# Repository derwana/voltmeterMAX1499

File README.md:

# voltmeterMAX1499
The voltmeterMAX1499 is - as you may expect by the name - a voltmeter based on the MAX1499 chip by maximinterated.

Started as a university project (v1) to be put into the student laboratories consoles as a highly accurat voltmeter (guess what: it never happend), it later got reworked (v2) to be used with a refrence voltage and two different seven-segment-display-boards.

## 1 precepts
1. boards for the IC and the 'display' have to be seperate
2. board dimensions not given, but as small as possible
3. six seven-segments – one for the '-' and five for the digits
4. multiple options for displaying (0kR for selection)
	1. decimals by chip
	2. decimals by user
5. boards to be connected by male and female headers
6. drills for spacers and mounting
7. use smd parts

## 2 prototype pictures

## 3 prototype testing
on X3: 5V DC (Vcc)
on X1: 1.000V DC (testvoltage by signalgenerator)

Measuring the current consumption is a good tool to determin a correctly working board.

One seven-segment-element consumes 20mA on max brightness and all tiles lit. Six of them are used, so a current consumption of ca. 120mA is expected.

With R3=24kR and displaying 18882, the current flowing is 117mA.
On idle, current consumption as expected of the datasheet.

## 4 Costs
estimated 45,00 € (per unit)
* PCBs 16.65€
* MAX1499 13.10€
* 7-Segments 1.00€-2.00€ (per segment-unit)

## 5 pictures of v2
Connections:
* potentiometer for dimming (black/pink)
* Vcc (black/red)
* voltage to measure (black/orange)
* programming interface (brown/red/orange/yellow)

## 6 further possible improvements (by programming)
* moving decimal point
* using internal reference of MAX1499
* reading measurements over serial

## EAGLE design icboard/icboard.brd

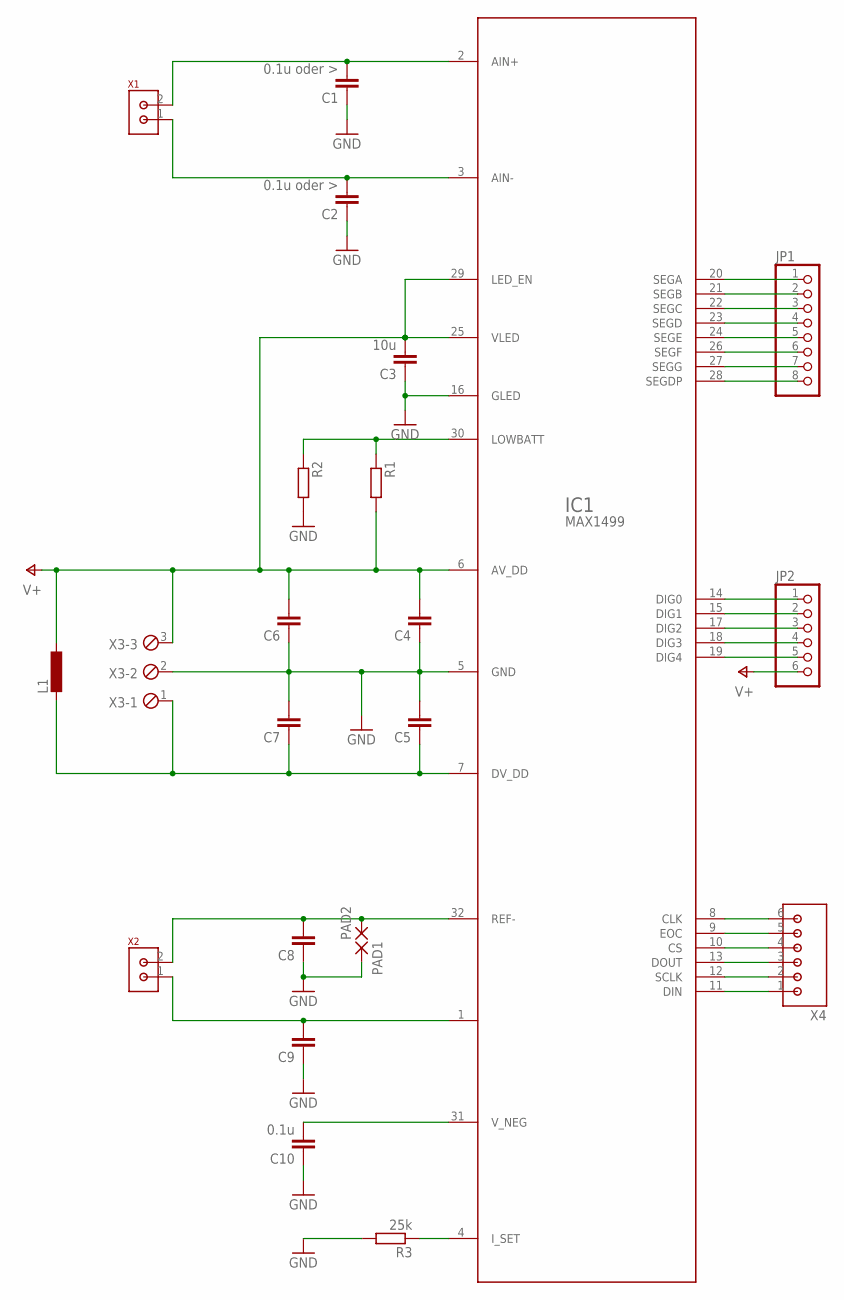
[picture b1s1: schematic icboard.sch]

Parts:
C1, C2: 0.1u oder >; C0603
C3: 10u; C0603
C4, C5, C6, C7, C8, C9: C-EUC0603; C0603
C10: 0.1u; C0603
IC1: MAX1499; TQFP32-08
JP1: PINHD-1X8; 1X08
JP2: PINHD-1X6; 1X06
L1: L-EUL1812; L1812
PAD1, PAD2: SMD2; SMD1,27-2,54
R1, R2: R-EU_R0603; R0603
R3: 25k; R0603
X1, X2: MOLEX_CON2_2P; CON2_2P
X3: MPT3; 3POL254
X4: MOLEX_CON2_6P; CON2_6P

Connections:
GND: C1.1, C2.1, C3.1, C4.1, C5.2, C6.1, C7.2, C8.1, C9.1, C10.1, IC1.5 (GND), IC1.16 (GLED), PAD1.1, R2.2, R3.2, X3.2
unnamed: C1.2, IC1.2 (AIN+), X1.2
unnamed: C2.2, IC1.3 (AIN-), X1.1
unnamed: IC1.17 (DIG2), JP2.3
unnamed: IC1.30 (LOWBATT), R1.1, R2.1
unnamed: C5.1, C7.1, IC1.7 (DV_DD), L1.2, X3.1
unnamed: C8.2, IC1.32 (REF-), PAD2.1, X2.2
unnamed: C9.2, IC1.1 (REF+), X2.1
unnamed: IC1.4 (I_SET), R3.1
unnamed: C10.2, IC1.31 (V_NEG)
unnamed: IC1.20 (SEGA), JP1.1
unnamed: IC1.21 (SEGB), JP1.2
unnamed: IC1.22 (SEGC), JP1.3
unnamed: IC1.23 (SEGD), JP1.4
unnamed: IC1.24 (SEGE), JP1.5
unnamed: IC1.26 (SEGF), JP1.6
unnamed: IC1.27 (SEGG), JP1.7
unnamed: IC1.28 (SEGDP), JP1.8
unnamed: IC1.14 (DIG0), JP2.1
unnamed: IC1.15 (DIG1), JP2.2
unnamed: IC1.18 (DIG3), JP2.4
unnamed: IC1.19 (DIG4), JP2.5
unnamed: IC1.9 (EOC), X4.5
unnamed: IC1.13 (DOUT), X4.3
unnamed: IC1.12 (SCLK), X4.2
unnamed: IC1.10 (CS), X4.4
unnamed: IC1.11 (DIN), X4.1
unnamed: IC1.8 (CLK), X4.6
V+: C3.2, C4.2, C6.2, IC1.6 (AV_DD), IC1.25 (VLED), IC1.29 (LED_EN), JP2.6, L1.1, R1.2, X3.3

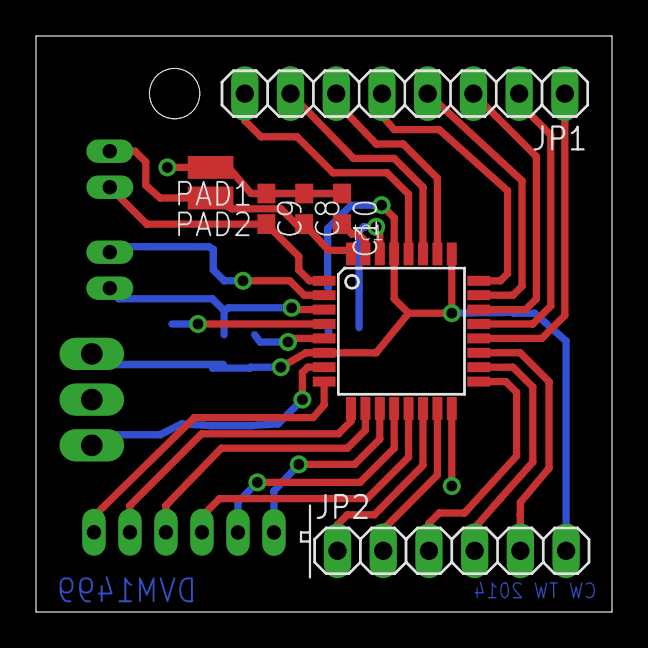
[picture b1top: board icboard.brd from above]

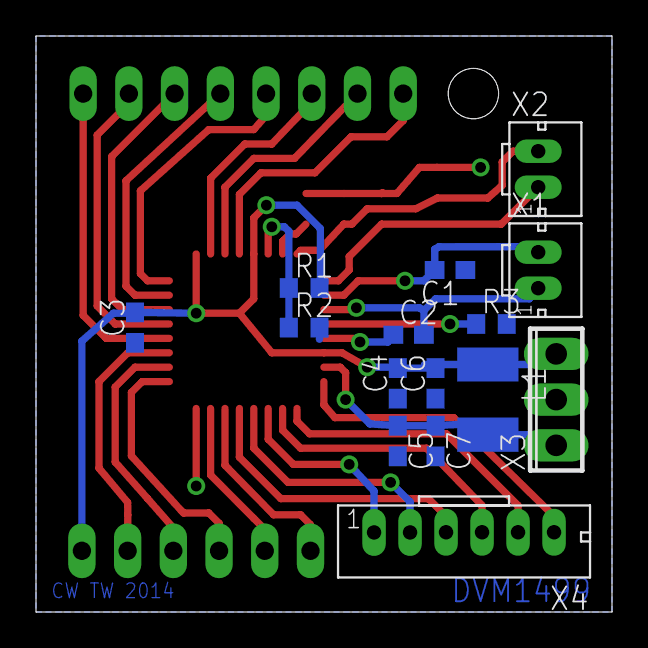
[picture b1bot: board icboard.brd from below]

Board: 2 copper layers, 32.0 x 32.0 mm, 23 parts (15 on the bottom side), 29 nets.

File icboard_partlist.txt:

Partlist

Assembly variant: 

Part     Value          Device        Package      Library         Sheet

C1       0.1u oder >    C-EUC0603     C0603        rcl             1
C2       0.1u oder >    C-EUC0603     C0603        rcl             1
C3       10u            C-EUC0603     C0603        rcl             1
C4                      C-EUC0603     C0603        rcl             1
C5                      C-EUC0603     C0603        rcl             1
C6                      C-EUC0603     C0603        rcl             1
C7                      C-EUC0603     C0603        rcl             1
C8                      C-EUC0603     C0603        rcl             1
C9                      C-EUC0603     C0603        rcl             1
C10      0.1u           C-EUC0603     C0603        rcl             1
IC1      MAX1499        MAX1499       TQFP32-08    LEDVoltmeter    1
JP1                     PINHD-1X8     1X08         pinhead         1
JP2                     PINHD-1X6     1X06         pinhead         1
L1                      L-EUL1812     L1812        rcl             1
PAD1                    SMD2          SMD1,27-2,54 wirepad         1
PAD2                    SMD2          SMD1,27-2,54 wirepad         1
R1                      R-EU_R0603    R0603        rcl             1
R2                      R-EU_R0603    R0603        rcl             1
R3       25k            R-EU_R0603    R0603        rcl             1
X1       MOLEX_CON2_2P  MOLEX_CON2_2P CON2_2P      Lib_Eis_HSW     1
X2       MOLEX_CON2_2P  MOLEX_CON2_2P CON2_2P      Lib_Eis_HSW     1
X3                      MPT3          3POL254      con-phoenix-254 1
X4                      MOLEX_CON2_6P CON2_6P      Lib_Eis_HSW     1

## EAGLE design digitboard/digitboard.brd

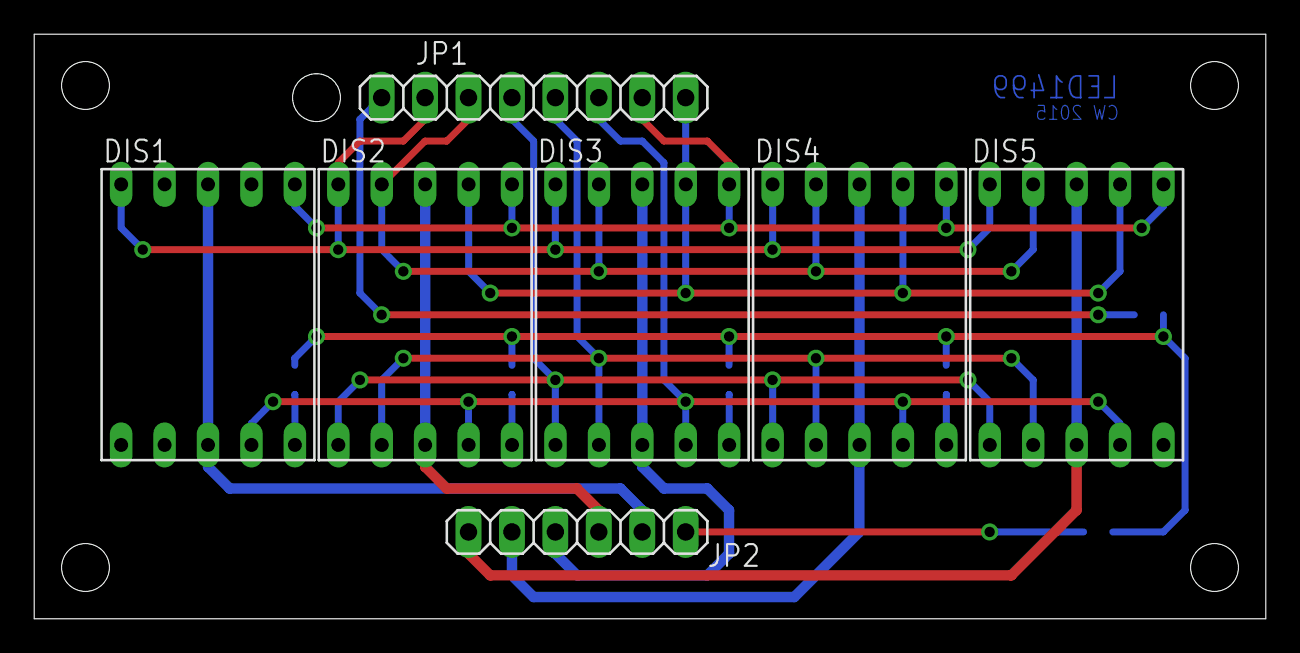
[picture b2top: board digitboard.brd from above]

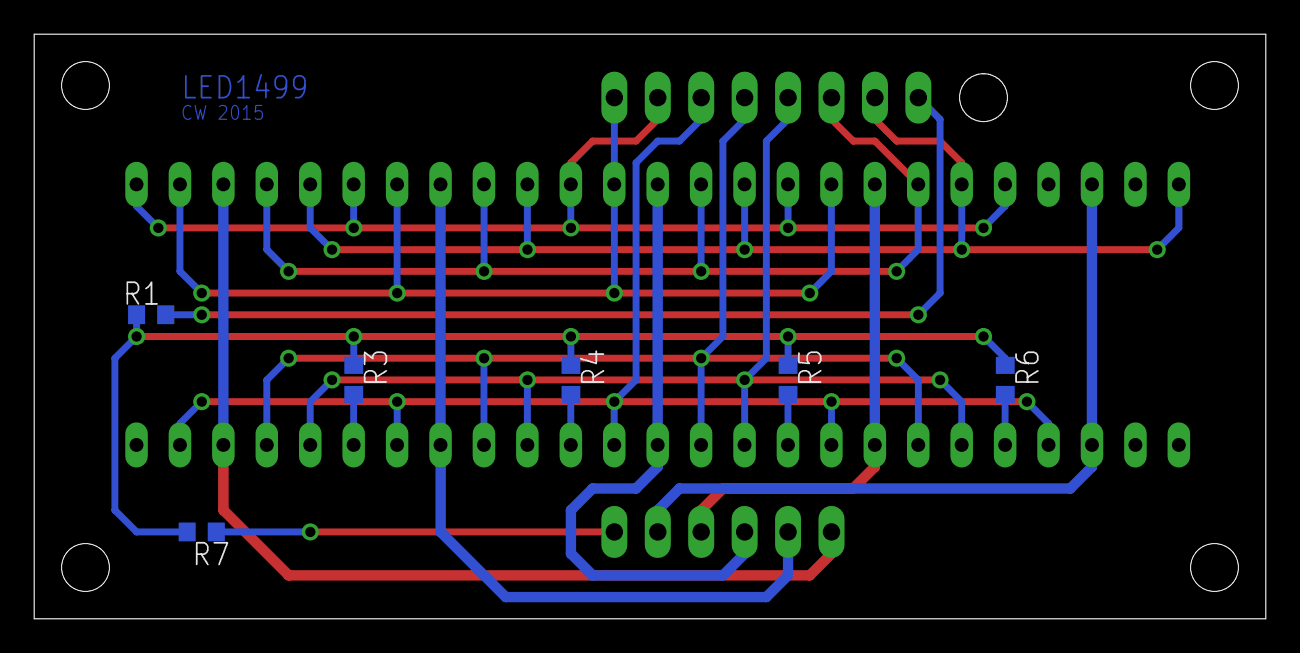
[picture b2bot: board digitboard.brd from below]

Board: 2 copper layers, 72.0 x 34.2 mm, 13 parts (6 on the bottom side), 19 nets.

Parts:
DIS1, DIS2, DIS3, DIS4, DIS5: HD-H103; HDSP-M
JP1: 1X08
JP2: 1X06
R1, R3, R4, R5, R6, R7: R0603

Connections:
unnamed: JP2.6, R7.2
unnamed: R1.2, R3.1, R4.1, R5.1, R6.1, R7.1
unnamed: JP1.8, R1.1
unnamed: DIS4.5, R3.2
unnamed: DIS3.5, R4.2
unnamed: DIS2.5, R5.2
unnamed: DIS1.5, R6.2
unnamed: DIS2.7, DIS3.7, DIS4.7, DIS5.7, JP1.1
unnamed: DIS1.6, DIS2.6, DIS3.6, DIS4.6, DIS5.6, JP1.2
unnamed: DIS1.4, DIS2.4, DIS3.4, DIS4.4, DIS5.4, JP1.3
unnamed: DIS2.2, DIS3.2, DIS4.2, DIS5.2, JP1.4
unnamed: DIS2.1, DIS3.1, DIS4.1, DIS5.1, JP1.5
unnamed: DIS2.9, DIS3.9, DIS4.9, DIS5.9, JP1.6
unnamed: DIS1.10, DIS2.10, DIS3.10, DIS4.10, DIS5.10, JP1.7
unnamed: DIS5.3, DIS5.8, JP2.1
unnamed: DIS4.3, DIS4.8, JP2.2
unnamed: DIS3.3, DIS3.8, JP2.3
unnamed: DIS2.3, DIS2.8, JP2.4
unnamed: DIS1.3, DIS1.8, JP2.5

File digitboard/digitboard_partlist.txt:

Partlist

Assembly variant: 

Part     Value          Device     Package  Sheet

DIS1     HD-H103        HD-H103    HDSP-M   1
DIS2     HD-H103        HD-H103    HDSP-M   1
DIS3     HD-H103        HD-H103    HDSP-M   1
DIS4     HD-H103        HD-H103    HDSP-M   1
DIS5     HD-H103        HD-H103    HDSP-M   1
JP1                     PINHD-1X8  1X08     1
JP2                     PINHD-1X6  1X06     1
R1                      R-EU_R0603 R0603    1
R3                      R-EU_R0603 R0603    1
R4                      R-EU_R0603 R0603    1
R5                      R-EU_R0603 R0603    1
R6                      R-EU_R0603 R0603    1
R7                      R-EU_R0603 R0603    1

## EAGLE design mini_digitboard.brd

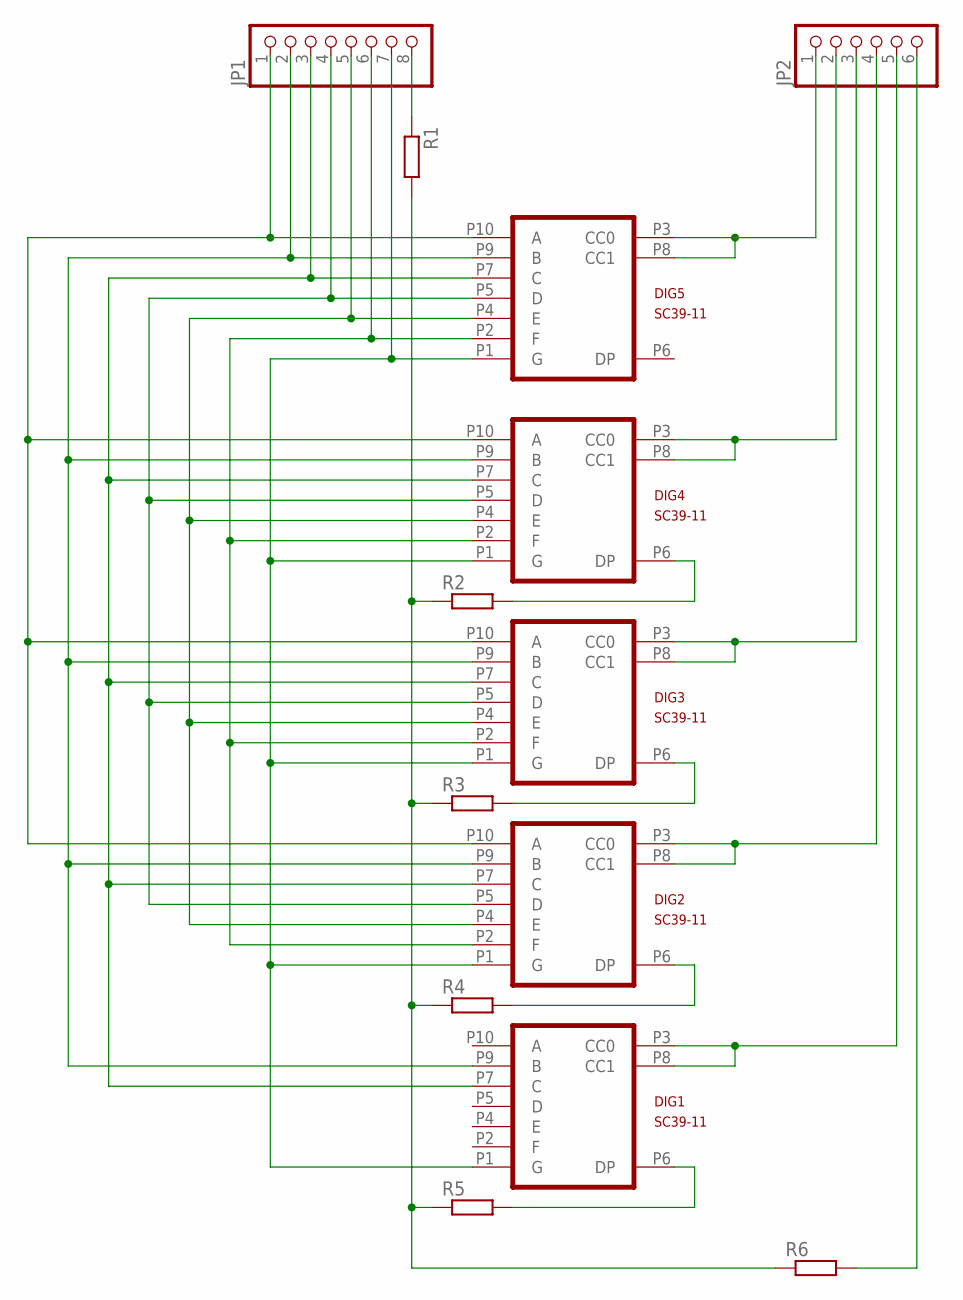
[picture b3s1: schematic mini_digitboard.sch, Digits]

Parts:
DIG1, DIG2, DIG3, DIG4, DIG5: SC39-11
JP1: PINHD-1X8; 1X08
JP2: PINHD-1X6; 1X06
R1, R2, R3, R4, R5, R6: R-EU_R0603; R0603

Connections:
unnamed: JP2.6, R6.2
unnamed: R1.2, R2.1, R3.1, R4.1, R5.1, R6.1
unnamed: JP1.8, R1.1
unnamed: DIG4.P6 (DP), R2.2
unnamed: DIG3.P6 (DP), R3.2
unnamed: DIG2.P6 (DP), R4.2
unnamed: DIG1.P6 (DP), R5.2
unnamed: DIG1.P1 (G), DIG2.P1 (G), DIG3.P1 (G), DIG4.P1 (G), DIG5.P1 (G), JP1.7
unnamed: DIG2.P10 (A), DIG3.P10 (A), DIG4.P10 (A), DIG5.P10 (A), JP1.1
unnamed: DIG1.P9 (B), DIG2.P9 (B), DIG3.P9 (B), DIG4.P9 (B), DIG5.P9 (B), JP1.2
unnamed: DIG1.P7 (C), DIG2.P7 (C), DIG3.P7 (C), DIG4.P7 (C), DIG5.P7 (C), JP1.3
unnamed: DIG2.P5 (D), DIG3.P5 (D), DIG4.P5 (D), DIG5.P5 (D), JP1.4
unnamed: DIG2.P4 (E), DIG3.P4 (E), DIG4.P4 (E), DIG5.P4 (E), JP1.5
unnamed: DIG2.P2 (F), DIG3.P2 (F), DIG4.P2 (F), DIG5.P2 (F), JP1.6
unnamed: DIG5.P3 (CC0), DIG5.P8 (CC1), JP2.1
unnamed: DIG4.P3 (CC0), DIG4.P8 (CC1), JP2.2
unnamed: DIG3.P3 (CC0), DIG3.P8 (CC1), JP2.3
unnamed: DIG2.P3 (CC0), DIG2.P8 (CC1), JP2.4
unnamed: DIG1.P3 (CC0), DIG1.P8 (CC1), JP2.5

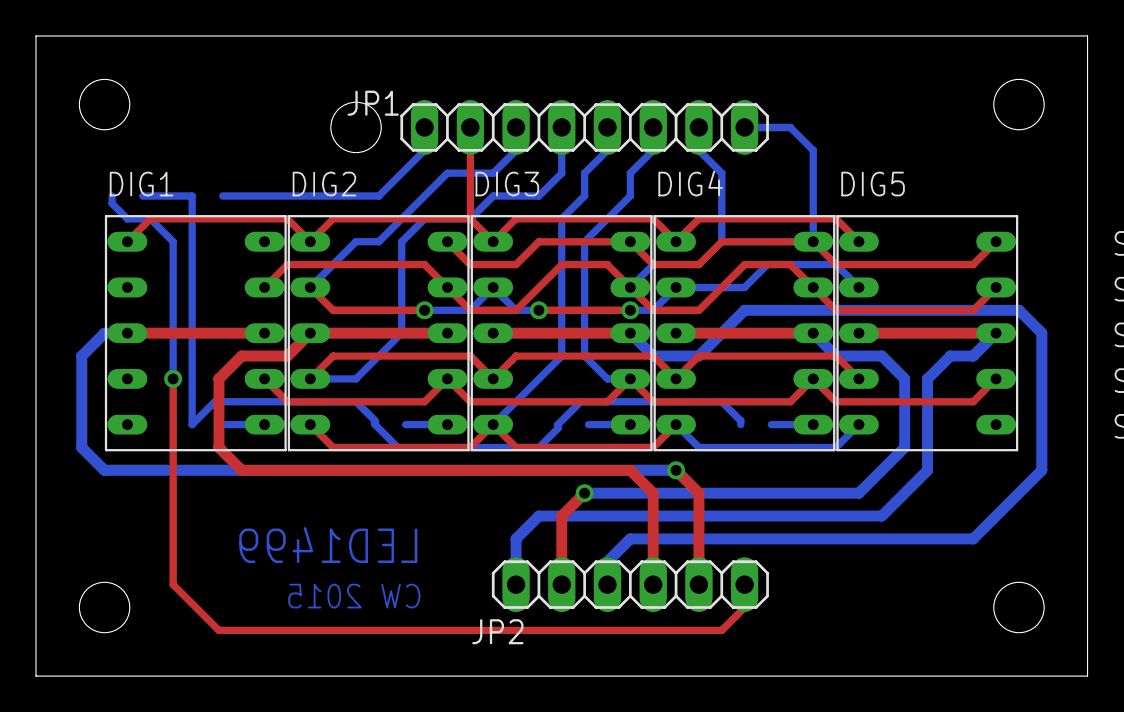
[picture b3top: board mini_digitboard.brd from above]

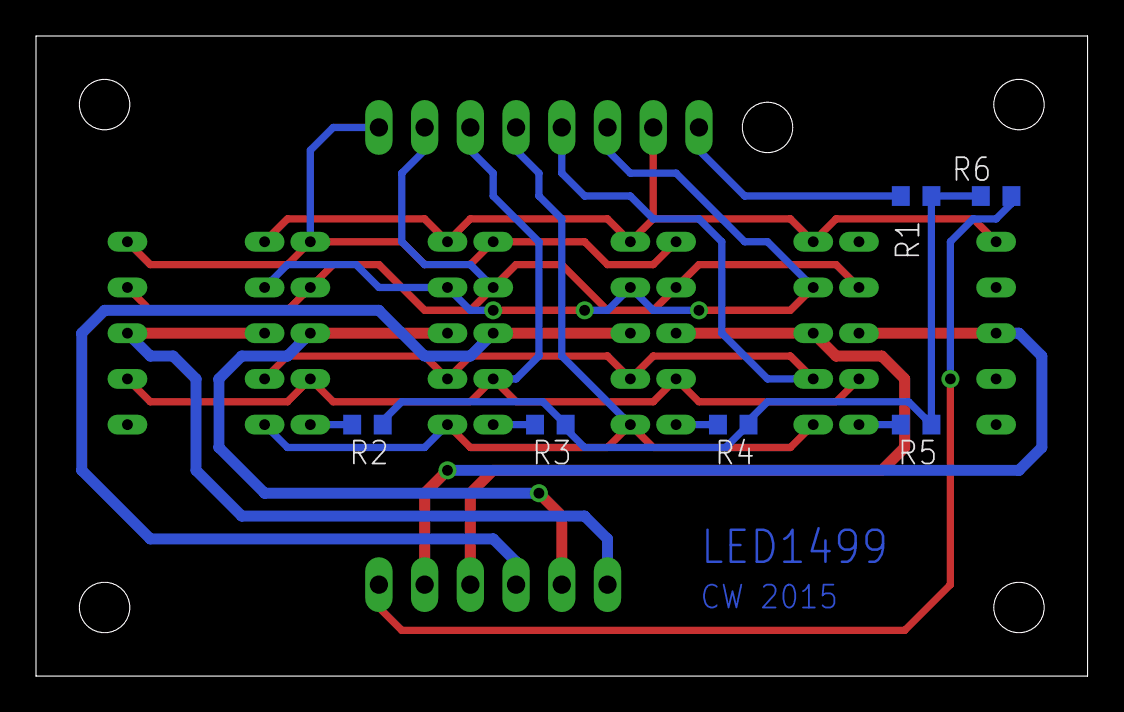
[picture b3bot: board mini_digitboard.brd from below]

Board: 2 copper layers, 58.4 x 35.6 mm, 13 parts (6 on the bottom side), 19 nets.

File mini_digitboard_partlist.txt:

Partlist

Exported from mini_digitboard.sch at 2/2/20 9:24 PM

EAGLE Version 9.5.2 Copyright (c) 1988-2019 Autodesk, Inc.

Assembly variant: 

Part     Value          Device     Package  Library      Sheet

DIG1     SC39-11        SC39-11    SC39-11  LEDVoltmeter 1
DIG2     SC39-11        SC39-11    SC39-11  LEDVoltmeter 1
DIG3     SC39-11        SC39-11    SC39-11  LEDVoltmeter 1
DIG4     SC39-11        SC39-11    SC39-11  LEDVoltmeter 1
DIG5     SC39-11        SC39-11    SC39-11  LEDVoltmeter 1
JP1                     PINHD-1X8  1X08     pinhead      1
JP2                     PINHD-1X6  1X06     pinhead      1
R1                      R-EU_R0603 R0603    rcl          1
R2                      R-EU_R0603 R0603    rcl          1
R3                      R-EU_R0603 R0603    rcl          1
R4                      R-EU_R0603 R0603    rcl          1
R5                      R-EU_R0603 R0603    rcl          1
R6                      R-EU_R0603 R0603    rcl          1

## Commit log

2020-02-02 added *.brd and *.sch files
2020-02-02 added pdfs of boards and schematics
2020-02-02 added pngs of boards and schematics
2020-02-02 added partlists
2020-02-02 added libraries of parts used
2020-02-02 added digitboard *.brd and *.sch
2020-02-02 added digitboard pdfs and pngs
2020-02-02 added digitboard partlist and library
2020-02-02 added mini_digitboard *.brd and *.sch
2020-02-02 added mini_digitboard pdfs and pngs
2020-02-02 added mini_digitboard partlist and library
2020-02-02 added icboard *.brd and *.sch
2020-02-02 added icboard pdfs and pngs
2020-02-02 added icboard partlist and library
2020-02-02 added folder structure
2020-02-02 added pictures of prototype
2020-02-02 added diffuser drawing
    to be placed on top of the 7-segments for better readability
2020-02-02 added some datasheets
2020-02-27 readme added
2020-02-27 adding v2 pictures
2020-02-27 added more readme
2020-02-27 changed paragraph title
2020-02-27 moved library to its folder
